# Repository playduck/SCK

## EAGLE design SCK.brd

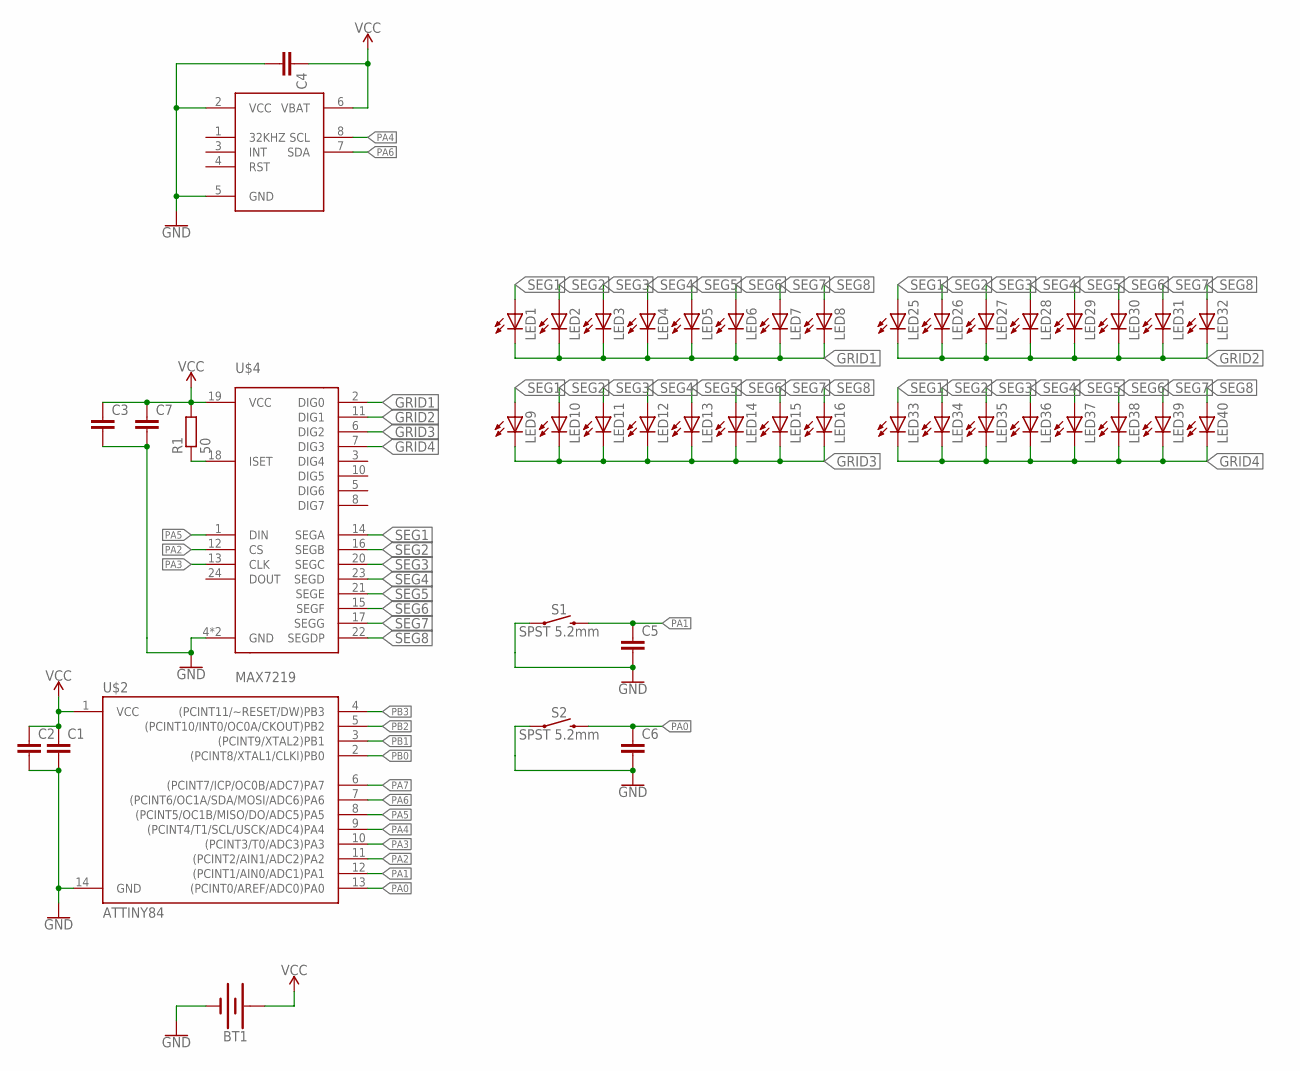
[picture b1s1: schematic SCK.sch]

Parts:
BT1: BATTERY-20MM_SMD_4LEGS; BATTCON_20MM_4LEGS
C1, C2, C3, C4, C5, C6, C7: C-EUC0805; C0805
LED1, LED2, LED3, LED4, LED5, LED6, LED7, LED8, LED9, LED10, LED11, LED12, LED13, LED14, LED15, LED16, LED25, LED26, LED27, LED28, LED29, LED30, LED31, LED32, LED33, LED34, LED35, LED36, LED37, LED38, LED39, LED40: LEDCHIPLED_0805; CHIPLED_0805
R1: 50; R0805
S1, S2: SPST 5.2mm; TACTILE_SWITCH_SMD_4.6X2.8MM
U$2: ATTINY84; SOIC127P599X175-14
U$3: DS3231M; SOIC127P600X175-8
U$4: MAX7219; SOIC127P1032X265-24

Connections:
GND: BT1.NEGATIVE (-), C1.2, C2.2, C3.2, C4.2, C5.2, C6.2, C7.2, S1.1, S1.2 (1), S2.1, S2.2 (1), U$2.14 (GND), U$3.2 (VCC), U$3.5 (GND), U$4.4 (GND), U$4.9 (GND)
GRID1: LED1.C, LED2.C, LED3.C, LED4.C, LED5.C, LED6.C, LED7.C, LED8.C, U$4.2 (DIG0)
GRID2: LED25.C, LED26.C, LED27.C, LED28.C, LED29.C, LED30.C, LED31.C, LED32.C, U$4.11 (DIG1)
GRID3: LED9.C, LED10.C, LED11.C, LED12.C, LED13.C, LED14.C, LED15.C, LED16.C, U$4.6 (DIG2)
GRID4: LED33.C, LED34.C, LED35.C, LED36.C, LED37.C, LED38.C, LED39.C, LED40.C, U$4.7 (DIG3)
unnamed: R1.1, U$4.18 (ISET)
PA0: C6.1, S2.3 (2), S2.4 (2), U$2.13 ((PCINT0/AREF/ADC0)PA0)
PA1: C5.1, S1.3 (2), S1.4 (2), U$2.12 ((PCINT1/AIN0/ADC1)PA1)
PA2: U$2.11 ((PCINT2/AIN1/ADC2)PA2), U$4.12 (CS)
PA3: U$2.10 ((PCINT3/T0/ADC3)PA3), U$4.13 (CLK)
PA4: U$2.9 ((PCINT4/T1/SCL/USCK/ADC4)PA4), U$3.8 (SCL)
PA5: U$2.8 ((PCINT5/OC1B/MISO/DO/ADC5)PA5), U$4.1 (DIN)
PA6: U$2.7 ((PCINT6/OC1A/SDA/MOSI/ADC6)PA6), U$3.7 (SDA)
PA7: U$2.6 ((PCINT7/ICP/OC0B/ADC7)PA7)
PB0: U$2.2 ((PCINT8/XTAL1/CLKI)PB0)
PB1: U$2.3 ((PCINT9/XTAL2)PB1)
PB2: U$2.5 ((PCINT10/INT0/OC0A/CKOUT)PB2)
PB3: U$2.4 ((PCINT11/~RESET/DW)PB3)
SEG1: LED1.A, LED9.A, LED25.A, LED33.A, U$4.14 (SEGA)
SEG2: LED2.A, LED10.A, LED26.A, LED34.A, U$4.16 (SEGB)
SEG3: LED3.A, LED11.A, LED27.A, LED35.A, U$4.20 (SEGC)
SEG4: LED4.A, LED12.A, LED28.A, LED36.A, U$4.23 (SEGD)
SEG5: LED5.A, LED13.A, LED29.A, LED37.A, U$4.21 (SEGE)
SEG6: LED6.A, LED14.A, LED30.A, LED38.A, U$4.15 (SEGF)
SEG7: LED7.A, LED15.A, LED31.A, LED39.A, U$4.17 (SEGG)
SEG8: LED8.A, LED16.A, LED32.A, LED40.A, U$4.22 (SEGDP)
VCC: BT1.POSITIVE@1 (+), BT1.POSITIVE@2 (+), BT1.POSITIVE@3 (+), BT1.POSITIVE@4 (+), C1.1, C2.1, C3.1, C4.1, C7.1, R1.2, U$2.1 (VCC), U$3.6 (VBAT), U$4.19 (VCC)

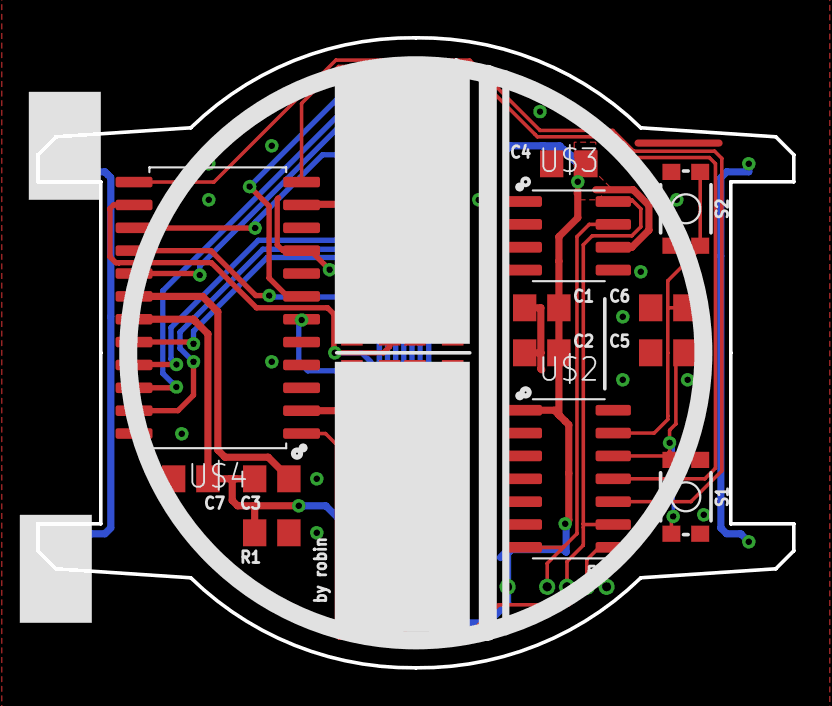
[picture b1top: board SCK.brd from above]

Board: 2 copper layers, 42.0 x 35.0 mm, 46 parts (1 on the bottom side), 22 nets.

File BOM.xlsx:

Quantity | Manufacture Part Number | Manufacturer(optional) | Description(optional) | LCSC Part Number(optional) | Package(optional)
1 | DS3231MZ+ | Maxim Integrated | RTC | C107410 | SOIC-8_150mil
1 | TM1637 | Shenzhen Titan Micro Elec | Led driver | C20001 | SOP-20_300mil
1 | ATTINY84A-SSU | Microchip Tech | microC | C144333 | SOIC-14_150mil
10 | 0805F104M500 | Huaxin S&T | 100nF Cap | C95395 | 805
2 | KMR231GLFS | C&K | button | C99271 | SMD,4.6x2.8x1.9mm
20 | D-B060306B1-KS2 | Wuxi ARK Tech Elec | blue led | C118339 | 603
20 | D-R060306L3-KS2 | Wuxi ARK Tech Elec | red led | C118330 | 603

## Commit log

2018-11-09 Added 3D Models

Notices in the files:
parts and their libraries:
SparkFun-Switches: Licensing: Creative Commons ShareAlike 4.0 International - https://creativecommons.org/licenses/by-sa/4.0
